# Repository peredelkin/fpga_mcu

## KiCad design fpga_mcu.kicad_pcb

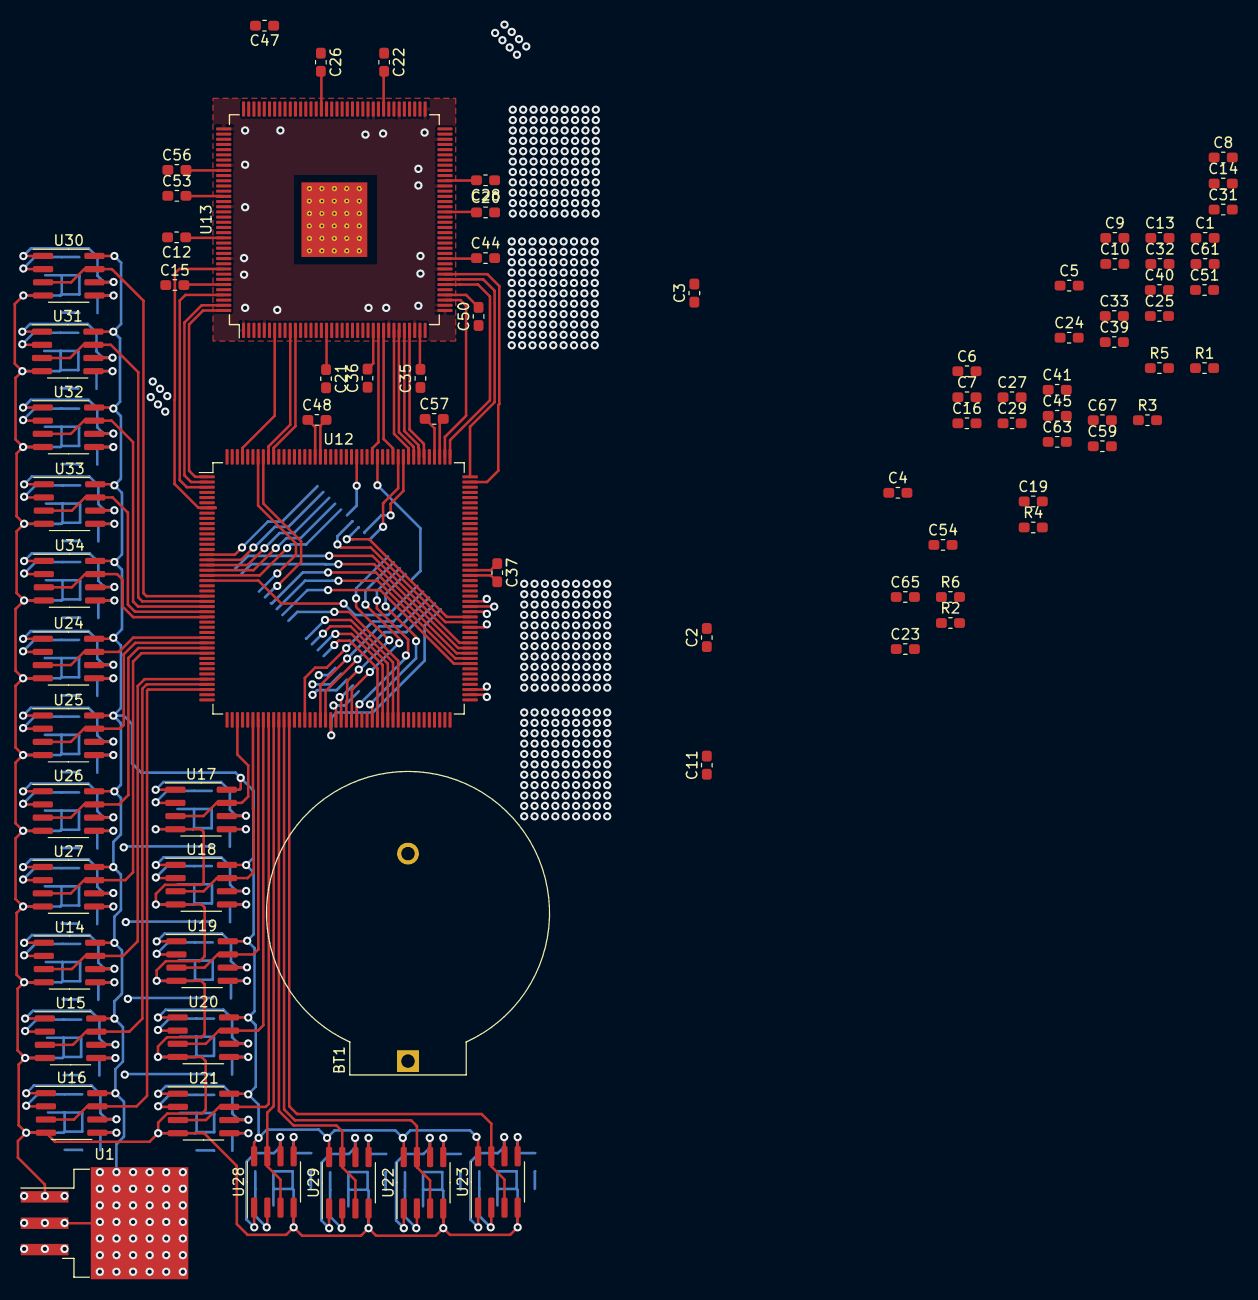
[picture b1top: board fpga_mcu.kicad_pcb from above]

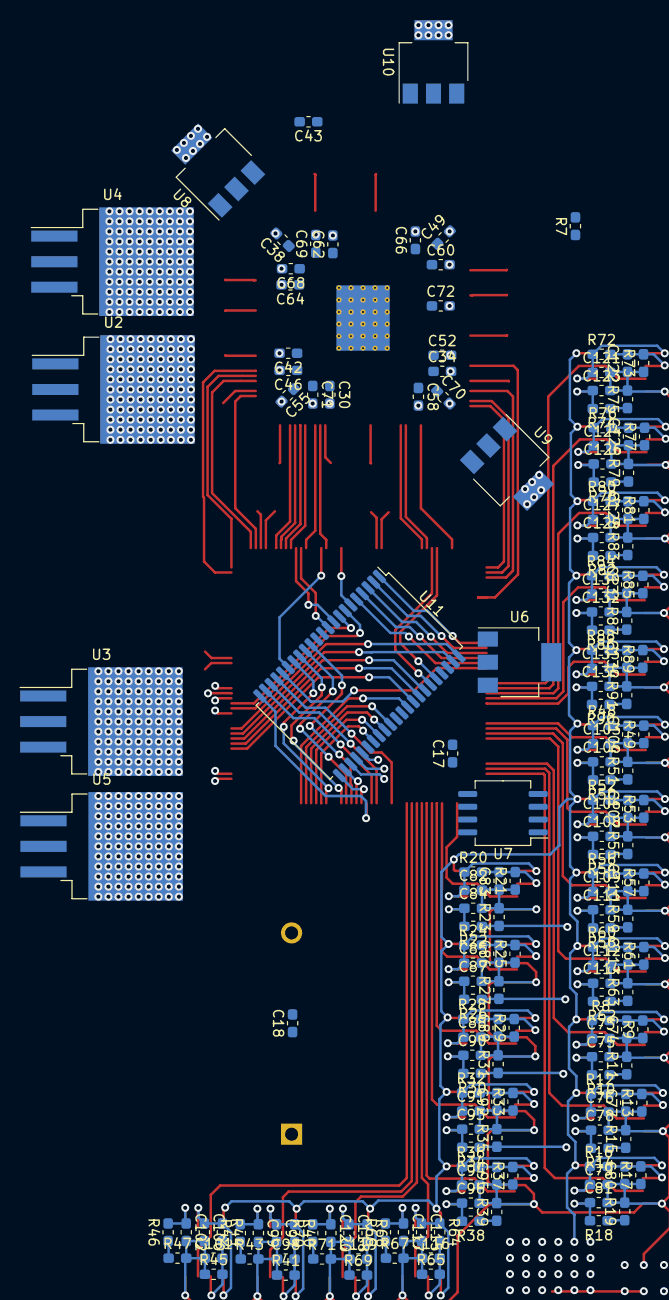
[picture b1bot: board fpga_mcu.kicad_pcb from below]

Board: 4 copper layers, 261 parts (179 on the bottom side), 173 nets.

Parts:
BT1: Battery_Cell; BatteryHolder_ComfortableElectronic_CH273-2450_1x2450
C1, C2, C3: 0.33uF; C_0603_1608Metric_Pad1.05x0.95mm_HandSolder
C4, C5, C6, C8, C9, C10, C11, C15, C16, C18, C20, C21, C22, C23, C24, C25, C26, C27, C28, C29, C30, C31, C32, C33, C34, C35, C36, C37, C38, C39, C40, C41, C42, C43, C44, C45, C46, C47, C48, C49, C50, C51, C52, C53, C54, C55, C56, C57, C58, C59, C60, C61, C62, C63, C64, C65, C66, C68, C69, C70, C71, C72, C73, C74, C76, C77, C79, C80, C82, C83, C85, C86, C88, C89, C91, C92, C94, C95, C97, C98, C100, C101, C103, C104, C106, C107, C109, C110, C112, C113, C115, C116, C118, C119, C121, C122, C124, C125, C127, C128, C130, C131, C133, C134: 0.1uF; C_0603_1608Metric_Pad1.05x0.95mm_HandSolder
C7, C12, C13, C14: 10uF; C_0603_1608Metric_Pad1.05x0.95mm_HandSolder
C17, C19: 1uF; C_0603_1608Metric_Pad1.05x0.95mm_HandSolder
C67: 4.7uF; C_0603_1608Metric_Pad1.05x0.95mm_HandSolder
C75, C78, C81, C84, C87, C90, C93, C96, C99, C102, C105, C108, C111, C114, C117, C120, C123, C126, C129, C132, C135: 0.05uF; C_0603_1608Metric_Pad1.05x0.95mm_HandSolder
R1, R2, R3, R5, R6: 0*; R_0603_1608Metric_Pad1.05x0.95mm_HandSolder
R4: 0; R_0603_1608Metric_Pad1.05x0.95mm_HandSolder
R7: 120; R_0603_1608Metric_Pad1.05x0.95mm_HandSolder
R8, R9, R10, R12, R13, R14, R16, R17, R18, R20, R21, R22, R24, R25, R26, R28, R29, R30, R32, R33, R34, R36, R37, R38, R40, R41, R42, R44, R45, R46, R48, R49, R50, R52, R53, R54, R56, R57, R58, R60, R61, R62, R64, R65, R66, R68, R69, R70, R72, R73, R74, R76, R77, R78, R80, R81, R82, R84, R85, R86, R88, R89, R90: 20k; R_0603_1608Metric_Pad1.05x0.95mm_HandSolder
R11, R15, R19, R23, R27, R31, R35, R39, R43, R47, R51, R55, R59, R63, R67, R71, R75, R79, R83, R87, R91: 1M; R_0603_1608Metric_Pad1.05x0.95mm_HandSolder
U1, U2, U3: LM1084-5.0; TO-263-3_TabPin2
U4, U5: LM1085-3.3; TO-263-3_TabPin2
U6: LD1117S33TR_SOT223; SOT-223-3_TabPin2
U7: REF192; SO-8_5.3x6.2mm_P1.27mm
U8, U9: LD1117S12TR_SOT223; SOT-223-3_TabPin2
U10: LD1117S25TR_SOT223; SOT-223-3_TabPin2
U11: IS61WV25616BLL; TSOP-II-44_10.16x18.41mm_P0.8mm
U12: STM32f429IGT; LQFP-176_24x24mm_P0.5mm
U13: EP4CE22E22I7N; EQFP-144-1EP_20x20mm_P0.5mm_EP7.2x6.35mm_ThermalVias
U14, U15, U16, U17, U18, U19, U20, U21, U22, U23, U24, U25, U26, U27, U28, U29, U30, U31, U32, U33, U34: AD8656; SOIC-8_3.9x4.9mm_P1.27mm

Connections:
/ADC3_IN4: U12.24, U30.3, U30.7
/ADC3_IN5: U12.25, U31.3, U31.7
/ADC3_IN6: U12.26, U32.3, U32.7
/ADC3_IN7: U12.27, U33.3, U33.7
/ADC3_IN8: U12.28, U34.3, U34.7
/ADC12_IN4: U12.50, U18.3, U18.7
/ADC12_IN5: U12.51, U19.3, U19.7
/ADC12_IN6: U12.52, U20.3, U20.7
/ADC12_IN7: U12.53, U21.3, U21.7
/ADC12_IN8: U12.56, U22.3, U22.7
/ADC12_IN9: U12.57, U23.3, U23.7
/ADC12_IN14: U12.54, U28.3, U28.7
/ADC12_IN15: U12.55, U29.3, U29.7
/ADC123_IN0: U12.40, U14.3, U14.7
/ADC123_IN1: U12.41, U15.3, U15.7
/ADC123_IN2: U12.42, U16.3, U16.7
/ADC123_IN3: U12.47, U17.3, U17.7
/ADC123_IN10: U12.32, U24.3, U24.7
/ADC123_IN11: U12.33, U25.3, U25.7
/ADC123_IN12: U12.34, U26.3, U26.7
/ADC123_IN13: U12.35, U27.3, U27.7
/FSMC_A0: U11.1, U12.16
/FSMC_A1: U11.2, U12.17
/FSMC_A2: U11.3, U12.18
/FSMC_A3: U11.4, U12.19
/FSMC_A4: U11.5, U12.20
/FSMC_A5: U11.18, U12.21
/FSMC_A6: U11.19, U12.60
/FSMC_A7: U11.20, U12.63
/FSMC_A8: U11.21, U12.64
/FSMC_A9: U11.22, U12.65
/FSMC_A10: U11.23, U12.66
/FSMC_A11: U11.24, U12.67
/FSMC_A12: U11.25, U12.106
/FSMC_A13: U11.26, U12.107
/FSMC_A14: U11.27, U12.108
/FSMC_A15: U11.42, U12.109
/FSMC_A16: U11.43, U12.99
/FSMC_A17: U11.44, U12.100
/FSMC_D0: U11.7, U12.104
/FSMC_D1: U11.8, U12.105
/FSMC_D2: U11.9, U12.142
/FSMC_D3: U11.10, U12.143
/FSMC_D4: U11.13, U12.68
/FSMC_D5: U11.14, U12.69
/FSMC_D6: U11.15, U12.70
/FSMC_D7: U11.16, U12.73
/FSMC_D8: U11.29, U12.74
/FSMC_D9: U11.30, U12.75
/FSMC_D10: U11.31, U12.76
/FSMC_D11: U11.32, U12.77
/FSMC_D12: U11.35, U12.78
/FSMC_D13: U11.36, U12.96
/FSMC_D14: U11.37, U12.97
/FSMC_D15: U11.38, U12.98
/FSMC_NBL0: U11.39, U12.169
/FSMC_NBL1: U11.40, U12.170
/FSMC_NE1: U11.6, U12.151
/FSMC_nOE: U11.41, U12.146
/FSMC_nWE: U11.17, U12.147
/HWAG_GAP_OUT: U12.168, U13.10
/HWAG_RST: U12.173, U13.7
/HWAG_SPI_CRC: U12.144, U13.28
/HWAG_VR_OUT: U12.167, U13.11
/IN1: R10.1, R11.1
/IN2: R14.1, R15.1
/IN3: R18.1, R19.1
/IN4: R22.1, R23.1
/IN5: R26.1, R27.1
/IN6: R30.1, R31.1
/IN7: R34.1, R35.1
/IN8: R38.1, R39.1
/IN9: R42.1, R43.1
/IN10: R46.1, R47.1
/IN11: R50.1, R51.1
/IN12: R54.1, R55.1
/IN13: R58.1, R59.1
/IN14: R62.1, R63.1
/IN15: R66.1, R67.1
/IN16: R70.1, R71.1
/IN17: R74.1, R75.1
/IN18: R78.1, R79.1
/IN19: R82.1, R83.1
/IN20: R86.1, R87.1
/IN21: R90.1, R91.1
/SPI2_MISO: U12.133, U13.42
/SPI2_MOSI: U12.134, U13.39
/SPI2_NSS: U12.131, U13.44
/SPI2_SCK: U12.132, U13.43
/SPI3_MISO: U12.140, U13.31
/SPI3_MOSI: U12.141, U13.30
/SPI3_NSS: U12.138, U13.33
/SPI3_SCK: U12.139, U13.32
ANALOG_VCC: C4.1, R2.2, R3.2, U1.2, U14.8, U15.8, U16.8, U17.8, U18.8, U19.8, U20.8, U21.8, U22.8, U23.8, U24.8, U25.8, U26.8, U27.8, U28.8, U29.8, U30.8, U31.8, U32.8, U33.8, U34.8
FPGA_1.2V: C30.2, C34.2, C38.2, C42.2, C46.2, C49.2, C52.2, C55.2, C58.2, C60.2, C62.2, C64.2, C66.2, C68.2, C69.2, C70.2, C71.2, C72.2, R7.1, U8.2, U9.2, U13.1, U13.5, U13.29, U13.34, U13.37, U13.38, U13.45, U13.61, U13.70, U13.73, U13.78, U13.83, U13.84, U13.109, U13.116, U13.124, U13.134, U13.138
FPGA_2.5V: C31.2, C35.2, C39.2, C43.2, U10.2, U13.3, U13.35, U13.75, U13.107
FPGA_3.3V: C12.1, C15.2, C20.1, C21.1, C22.2, C26.2, C28.2, C32.2, C36.2, C40.1, C44.1, C47.2, C50.2, C53.2, C56.2, R5.1, U4.2, U8.3, U9.3, U10.3, U13.17, U13.26, U13.40, U13.47, U13.56, U13.62, U13.81, U13.93, U13.117, U13.122, U13.130, U13.139
FPGA_5V: C5.1, C10.1, R1.1, R2.1, U2.2, U4.3
GND: BT1.2, C1.2, C2.2, C3.2, C4.2, C5.2, C6.2, C7.2, C8.2, C9.2, C10.2, C11.2, C12.2, C13.2, C14.2, C15.1, C16.2, C17.2, C18.2, C19.2, C20.2, C21.2, C22.1, C23.2, C24.2, C25.2, C26.1, C27.2, C28.1, C29.2, C30.1, C31.1, C32.1, C33.2, C34.1, C35.1, C36.1, C37.2, C38.1, C39.1, C40.2, C41.2, C42.1, C43.1, C44.2, C45.2, C46.1, C47.1, C48.2, C49.1, C50.1, C51.2, C52.1, C53.1, C54.2, C55.1, C56.1, C57.2, C58.1, C59.2, C60.1, C61.2, C62.1, C63.2, C64.1, C65.2, C66.1, C67.2, C68.1, C69.1, C70.1, C71.1, C72.1, C73.2, C74.1, C75.2, C76.2, C77.1, C78.2, C79.2, C80.1, C81.2, C82.2, C83.1, C84.2, C85.2, C86.1, C87.2, C88.2, C89.1, C90.2, C91.2, C92.1, C93.2, C94.2, C95.1, C96.2, C97.2, C98.1, C99.2, C100.2, C101.1, C102.2, C103.2, C104.1, C105.2, C106.2, C107.1, C108.2, C109.2, C110.1, C111.2, C112.2, C113.1, C114.2, C115.2, C116.1, C117.2, C118.2, C119.1, C120.2, C121.2, C122.1, C123.2, C124.2, C125.1, C126.2, C127.2, C128.1, C129.2, C130.2, C131.1, C132.2, C133.2, C134.1, C135.2, R7.2, R9.1, R11.2, R13.1, R15.2, R17.1, R19.2, R21.1, R23.2, R25.1, R27.2, R29.1, R31.2, R33.1, R35.2, R37.1, R39.2, R41.1, R43.2, R45.1, R47.2, R49.1, R51.2, R53.1, R55.2, R57.1, R59.2, R61.1, R63.2, R65.1, R67.2, R69.1, R71.2, R73.1, R75.2, R77.1, R79.2, R81.1, R83.2, R85.1, R87.2, R89.1, R91.2, U1.1, U2.1, U3.1, U4.1, U5.1, U6.1, U7.4, U8.1, U9.1, U10.1, U11.12, U11.34, U12.14, U12.22, U12.37, U12.61, U12.71, U12.90, U12.102, U12.113, U12.126, U12.135, U12.148, U12.158, U13.2, U13.4, U13.19, U13.22, U13.27, U13.36, U13.41, U13.48, U13.57, U13.63, U13.74, U13.79, U13.82, U13.95, U13.108, U13.118, U13.123, U13.131, U13.140, U14.4, U15.4, U16.4, U17.4, U18.4, U19.4, U20.4, U21.4, U22.4, U23.4, U24.4, U25.4, U26.4, U27.4, U28.4, U29.4, U30.4, U31.4, U32.4, U33.4, U34.4
MCU_5V: C6.1, C7.1, C8.1, C9.1, C11.1, R1.2, R3.1, R4.2, U3.2, U5.3, U6.3, U7.2
MCU_12V: C1.1, C2.1, C3.1, U1.3, U2.3, U3.3
MCU_VBAT: BT1.1, C18.1
MCU_VDD: C13.1, C16.1, C23.1, C27.1, C29.1, C33.1, C37.1, C41.1, C45.1, C48.1, C51.1, C54.1, C57.1, C59.1, C61.1, C63.1, C65.1, C67.1, R5.2, R6.1, U5.2, U11.11, U11.33, U12.15, U12.23, U12.36, U12.49, U12.62, U12.72, U12.91, U12.103, U12.114, U12.127, U12.136, U12.149, U12.159, U12.172
MCU_VDDA: C14.1, C17.1, C24.1, R6.2, U6.2, U12.39
MCU_VREF: C19.1, C25.1, U7.6, U12.38
unnamed: C73.1, R8.1, U14.1, U14.6
unnamed: C74.2, R8.2, R9.2, U14.2
unnamed: C75.1, R10.2, U14.5
unnamed: C76.1, R12.1, U15.1, U15.6
unnamed: C77.2, R12.2, R13.2, U15.2
unnamed: C78.1, R14.2, U15.5
unnamed: C79.1, R16.1, U16.1, U16.6
unnamed: C80.2, R16.2, R17.2, U16.2
unnamed: C81.1, R18.2, U16.5
unnamed: C82.1, R20.1, U17.1, U17.6
unnamed: C83.2, R20.2, R21.2, U17.2
unnamed: C84.1, R22.2, U17.5
unnamed: C85.1, R24.1, U18.1, U18.6
unnamed: C86.2, R24.2, R25.2, U18.2
unnamed: C87.1, R26.2, U18.5
unnamed: C88.1, R28.1, U19.1, U19.6
unnamed: C89.2, R28.2, R29.2, U19.2
unnamed: C90.1, R30.2, U19.5
unnamed: C91.1, R32.1, U20.1, U20.6
unnamed: C92.2, R32.2, R33.2, U20.2
unnamed: C93.1, R34.2, U20.5
unnamed: C94.1, R36.1, U21.1, U21.6
unnamed: C95.2, R36.2, R37.2, U21.2
unnamed: C96.1, R38.2, U21.5
unnamed: C97.1, R40.1, U22.1, U22.6
unnamed: C98.2, R40.2, R41.2, U22.2
unnamed: C99.1, R42.2, U22.5
unnamed: C100.1, R44.1, U23.1, U23.6
unnamed: C101.2, R44.2, R45.2, U23.2
unnamed: C102.1, R46.2, U23.5
unnamed: C103.1, R48.1, U24.1, U24.6
unnamed: C104.2, R48.2, R49.2, U24.2
unnamed: C105.1, R50.2, U24.5
unnamed: C106.1, R52.1, U25.1, U25.6
unnamed: C107.2, R52.2, R53.2, U25.2
unnamed: C108.1, R54.2, U25.5
unnamed: C109.1, R56.1, U26.1, U26.6
unnamed: C110.2, R56.2, R57.2, U26.2
unnamed: C111.1, R58.2, U26.5
unnamed: C112.1, R60.1, U27.1, U27.6
unnamed: C113.2, R60.2, R61.2, U27.2
unnamed: C114.1, R62.2, U27.5
unnamed: C115.1, R64.1, U28.1, U28.6
unnamed: C116.2, R64.2, R65.2, U28.2
unnamed: C117.1, R66.2, U28.5
unnamed: C118.1, R68.1, U29.1, U29.6
unnamed: C119.2, R68.2, R69.2, U29.2
unnamed: C120.1, R70.2, U29.5
unnamed: C121.1, R72.1, U30.1, U30.6
unnamed: C122.2, R72.2, R73.2, U30.2
unnamed: C123.1, R74.2, U30.5
unnamed: C124.1, R76.1, U31.1, U31.6
unnamed: C125.2, R76.2, R77.2, U31.2
unnamed: C126.1, R78.2, U31.5
unnamed: C127.1, R80.1, U32.1, U32.6
unnamed: C128.2, R80.2, R81.2, U32.2
unnamed: C129.1, R82.2, U32.5
unnamed: C130.1, R84.1, U33.1, U33.6
unnamed: C131.2, R84.2, R85.2, U33.2
unnamed: C132.1, R86.2, U33.5
unnamed: C133.1, R88.1, U34.1, U34.6
unnamed: C134.2, R88.2, R89.2, U34.2
unnamed: C135.1, R90.2, U34.5
unnamed: R4.1, U7.3
unnamed: U12.1, U13.144
unnamed: U12.2, U13.143
unnamed: U12.3, U13.141
unnamed: U12.7, U13.136

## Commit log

2020-08-06 питание
2020-08-06 земля
2020-08-07 analog
2020-08-07 sram
2020-08-07 fpga
2020-08-07 fpga power
2020-08-08 power
2020-08-08 hwag pins
2020-08-10 f4 model
2020-08-10 opamp
2020-08-11 memory
2020-08-12 зоны
2020-08-12 fpga 1.2
2020-08-12 fpga зона запрета
2020-08-12 fpga 3.3
